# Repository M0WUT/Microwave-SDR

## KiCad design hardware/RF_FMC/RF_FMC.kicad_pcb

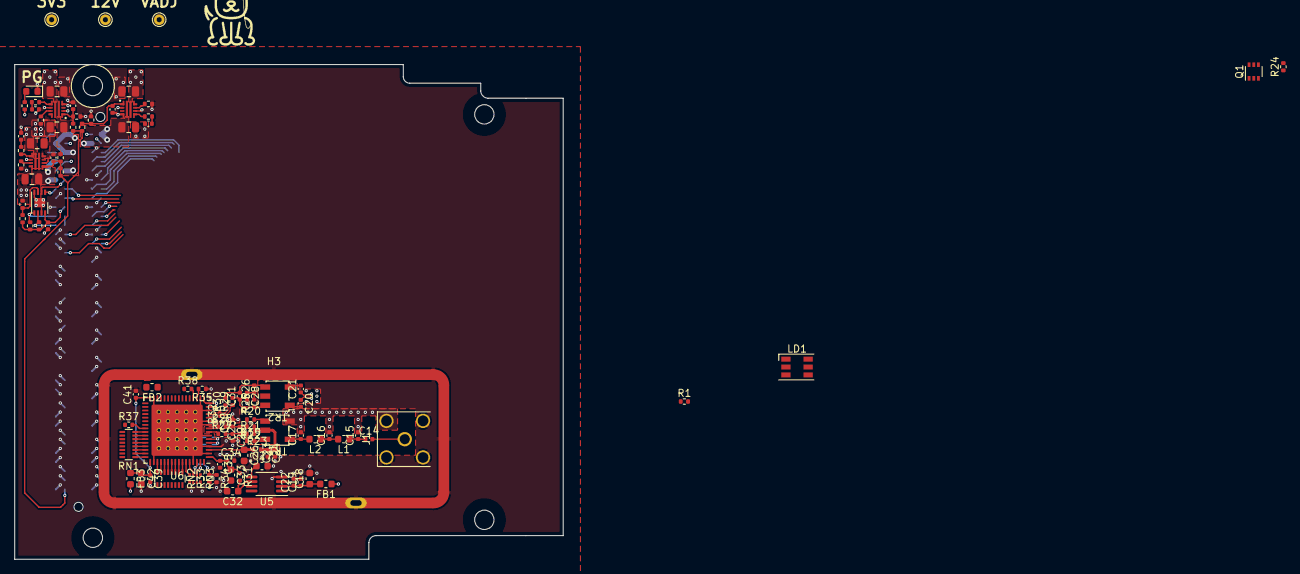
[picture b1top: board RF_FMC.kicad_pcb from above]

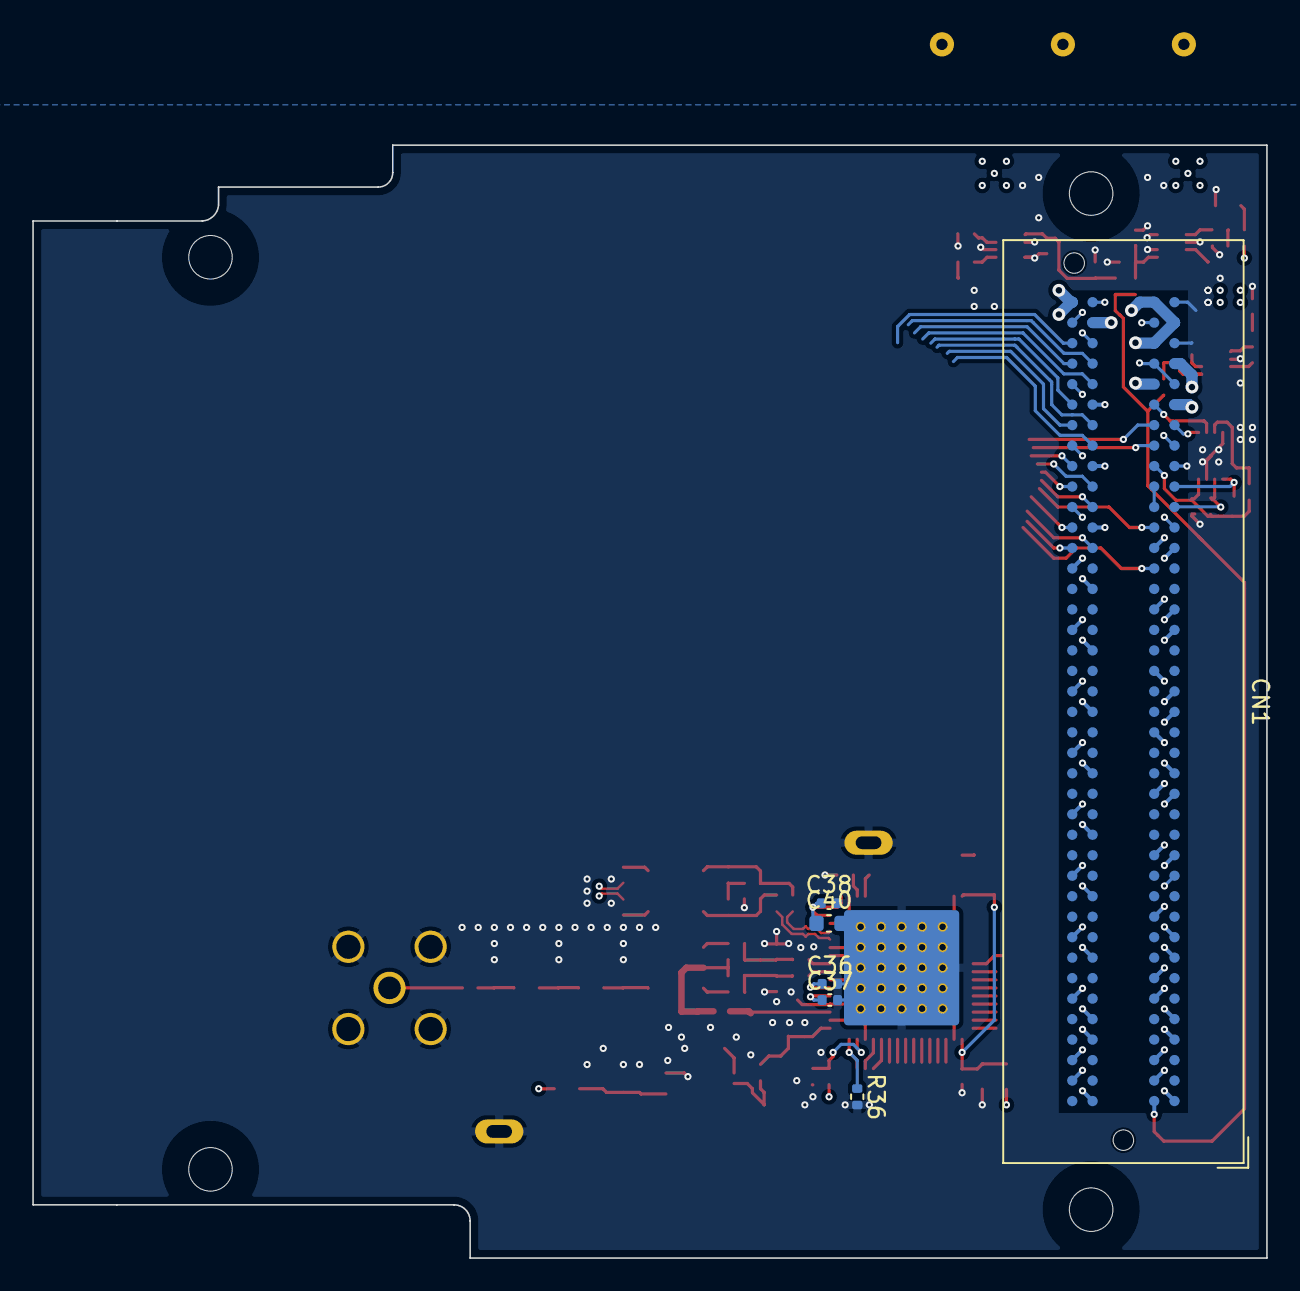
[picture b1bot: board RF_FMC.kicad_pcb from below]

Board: 4 copper layers, 76.5 x 69.0 mm, 108 parts (6 on the bottom side), 82 nets.

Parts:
C1, C14, C19, C20, C21, C24, C28, C34, C36, C37, C38, C39, C41: 100n; C_0402_1005Metric
C2, C3, C4, C11, C12, C13: 10u; C_0805_2012Metric
C5, C6, C7: DNF; C_0402_1005Metric
C8, C9, C10, C23: 10n; C_0402_1005Metric
C15, C17: 47p; C_0402_1005Metric
C16: 150p; C_0402_1005Metric
C18, C32, C33: 10u; C_0603_1608Metric
C22, C35: 1n; C_0402_1005Metric
C25, C29, C30, C31: 8p2; C_0402_1005Metric
C26: 2u2; C_0603_1608Metric
C27, C40, C42: 1u; C_0603_1608Metric
CN1: FMC_Mezzanine; Samtec_FMC_ASP-134604-01_4x40_Vertical
D1: LED; LED_0603_1608Metric
FB1, FB2, FB3: FerriteBead_Small; L_0603_1608Metric
H1, H2: MountingHole; MountingHole_2.7mm
H3: Shield; Shield_Masach_MS477-10_47.7x18.2x4mm_TH.step
J1: Conn_Coaxial; SMA_Linx_CONSMA002-L-G_Horizontal
L1, L2: 330n; L_0603_1608Metric
LD1: LED_Cree_CLX6E-FKC; LED_RGB_PLCC-6
M1: Logo_10mmx10mm
Q1: SI1539CDL-T1-GE3; SOT-363_SC-70-6
R1: R; R_0402_1005Metric
R2, R4, R5: DNF; R_0402_1005Metric
R3, R35: 0; R_0402_1005Metric
R6, R7, R8, R9: 1k; R_0402_1005Metric
R10, R11, R12: 100k; R_0402_1005Metric
R13, R14, R15: 100; R_0402_1005Metric
R16, R17, R18: 2k; R_0402_1005Metric
R19, R20: 10R; R_0402_1005Metric
R21, R22: 35R; R_0402_1005Metric
R23, R27, R28, R29, R30: 5R1; R_0402_1005Metric
R24: 22k; R_0402_1005Metric
R25, R26: 51R; R_0402_1005Metric
R31, R34, R36: 10k; R_0402_1005Metric
R32: 100R; R_0201_0603Metric
R33: 5k1; R_0402_1005Metric
R37, R38: 33; R_0402_1005Metric
RN1, RN2: 33; R_Array_Convex_8x0602
RN3: 33; R_Array_Convex_4x0402
TP1, TP2, TP3: TestPoint; TestPoint_THTPad_D1.5mm_Drill0.7mm
TR1, TR2: ETC1-1T-2TR; Macom_ETC-1xx
U1: 24LC02BT-I/MNY; DFN-8-1EP_3x2mm_P0.5mm_EP1.3x1.5mm
U2, U3, U4: LM73100RPWR; TI_LM73100_RPW
U5: REF5025IDGK; MSOP-8_3x3mm_P0.65mm
U6: LTC2216; QFN-64-1EP_9x9mm_P0.5mm_EP7.15x7.15mm

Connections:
3V3_AUX: C1.1, CN1.D32 (3P3VAUX), R2.1, R4.1, R5.1, U1.8 (VCC)
3V3_FMC: C3.1, CN1.C39 (3P3V), CN1.D36 (3P3V), CN1.D38 (3P3V), CN1.D40 (3P3V), U3.5 (IN)
12V_FMC: C2.1, CN1.C35 (12P0V), CN1.C37 (12P0V), U2.5 (IN)
+3.3VADC: FB1.1, FB2.2, LD1.4
+3V3: C12.1, R6.1, TP2.1, U3.6 (OUT)
+12V: C11.1, TP1.1, U2.6 (OUT)
/Direct Sampling ADC/ADC_Dither: R38.2, U6.20 (DITH)
/Direct Sampling ADC/ADC_N: C21.1, R1.2
/Direct Sampling ADC/ADC_P: C20.1, R1.1
/Direct Sampling ADC/ENC_N: R30.1, R32.2, U6.13 (ENC-)
/Direct Sampling ADC/ENC_P: R29.1, R32.1, U6.12 (ENC+)
/FMC Connector/FMC_SCL: CN1.C30 (SCL), R4.2, U1.6 (SCL)
/FMC Connector/FMC_SDA: CN1.C31 (SDA), R5.2, U1.5 (SDA)
/FMC Connector/GA0: CN1.C34 (GA0), U1.1 (A0)
/FMC Connector/GA1: CN1.D35 (GA1), U1.2 (A1)
/FMC Connector/PG_C2M: CN1.D1 (PG_C2M), R7.1, R8.1, R9.1
GND: C1.2, C2.2, C3.2, C4.2, C5.2, C6.2, C7.2, C8.2, C9.2, C10.2, C11.2, C12.2, C13.2, C15.2, C16.2, C17.2, C18.2, C19.2, C22.2, C23.1, C24.2, C26.2, C27.2, C28.2, C29.2, C30.2, C32.2, C33.2, C34.2, C35.2, C36.2, C37.2, C38.2, C39.2, C40.2, C41.2, C42.2, CN1.C1 (GND), CN1.C4 (GND), CN1.C5 (GND), CN1.C8 (GND), CN1.C9 (GND), CN1.C12 (GND), CN1.C13 (GND), CN1.C16 (GND), CN1.C17 (GND), CN1.C20 (GND), CN1.C21 (GND), CN1.C24 (GND), CN1.C25 (GND), CN1.C28 (GND), CN1.C29 (GND), CN1.C32 (GND), CN1.C33 (GND), CN1.C36 (GND), CN1.C38 (GND), CN1.C40 (GND), CN1.D2 (GND), CN1.D3 (GND), CN1.D6 (GND), CN1.D7 (GND), CN1.D10 (GND), CN1.D13 (GND), CN1.D16 (GND), CN1.D19 (GND), CN1.D22 (GND), CN1.D25 (GND), CN1.D28 (GND), CN1.D37 (GND), CN1.D39 (GND), CN1.G1 (GND), CN1.G4 (GND), CN1.G5 (GND), CN1.G8 (GND), CN1.G11 (GND), CN1.G14 (GND), CN1.G17 (GND), CN1.G20 (GND), CN1.G23 (GND), CN1.G26 (GND), CN1.G29 (GND), CN1.G32 (GND), CN1.G35 (GND), CN1.G38 (GND), CN1.G40 (GND), CN1.H2 (PRSNT_M2C_L), CN1.H3 (GND), CN1.H6 (GND), CN1.H9 (GND), CN1.H12 (GND), CN1.H15 (GND), CN1.H18 (GND), CN1.H21 (GND), CN1.H24 (GND), CN1.H27 (GND), CN1.H30 (GND), CN1.H33 (GND), CN1.H36 (GND), CN1.H39 (GND), D1.1 (K), H3.1, J1.2 (Ext), Q1.1, R3.2, R10.2, R11.2, R12.2, R16.2, R17.2, R18.2, R34.2, R35.1, R36.2, TR1.2, U1.4 (GND), U1.7 (WP), U1.9 (PAD), U2.2 (OVLO), U2.4 (PGTH), U2.8 (GND), U3.2 (OVLO), U3.4 (PGTH), U3.8 (GND), U4.2 (OVLO), U4.4 (PGTH), U4.8 (GND), U5.4 (GND), U6.2 (GND), U6.4 (GND), U6.7 (GND), U6.10 (GND), U6.11 (GND), U6.14 (GND), U6.18 (GND), U6.31 (OGND), U6.50 (OGND), U6.61 (LVDS), U6.65 (GND)
unnamed: C5.1, R7.2, R10.1, U2.1 (EN/UVLO)
unnamed: C6.1, R8.2, R11.1, U3.1 (EN/UVLO)
unnamed: C7.1, R9.2, R12.1, U4.1 (EN/UVLO)
unnamed: C8.1, R13.2
unnamed: C9.1, R14.2
unnamed: C10.1, R15.2
unnamed: C14.1, C15.1, L1.1
unnamed: C14.2, J1.1 (In)
unnamed: C16.1, L1.2, L2.1
unnamed: C17.1, L2.2, TR1.1
unnamed: C18.1, C19.1, C22.1, FB1.2, U5.2 (Vin)
unnamed: C20.2, TR2.1
unnamed: C21.2, TR2.2
unnamed: C23.2, C24.1, R21.2, R22.1, R23.2, TR1.4 (MP)
unnamed: C25.1, C29.1, R19.1, R21.1, R27.2
unnamed: C25.2, C30.1, R20.1, R22.2, R28.2
unnamed: C26.1, R23.1, U6.3 (VCM)
unnamed: C27.1, U5.5 (Trim/NR)
unnamed: C28.1, R25.2, R26.1
unnamed: C31.1, R25.1, R29.2, TR2.5
unnamed: C31.2, R26.2, R30.2, TR2.3
unnamed: C32.1, R31.2, U5.6 (Vout)
unnamed: C33.1, C34.1, C35.1, R31.1, U6.1 (Sense)
unnamed: CN1.D30 (TDI), CN1.D31 (TDO)
unnamed: D1.2 (A), R6.2
unnamed: LD1.3, R24.1
unnamed: Q1.6, R24.2
unnamed: R2.2, R3.1, U1.3 (A2)
unnamed: R13.1, U2.7 (DVDT)
unnamed: R14.1, U3.7 (DVDT)
unnamed: R15.1, U4.7 (DVDT)
unnamed: R16.1, U2.9 (IMON)
unnamed: R17.1, U3.9 (IMON)
unnamed: R18.1, U4.9 (IMON)
unnamed: R19.2, TR1.5
unnamed: R20.2, TR1.3
unnamed: R27.1, U6.8 (AIN+)
unnamed: R28.1, U6.9 (AIN-)
unnamed: R33.2, R34.1, U6.62 (Mode)
unnamed: R35.2, U6.19 (SHDN)
unnamed: R36.1, RN3.2 (R2.1), U6.63 (Rand)
unnamed: R37.2, U6.40 (ClkOutB)
unnamed: RN1.1 (R1.1), U6.48 (D6)
unnamed: RN1.2 (R2.1), U6.47 (D5)
unnamed: RN1.3 (R3.1), U6.46 (D4)
unnamed: RN1.4 (R4.1), U6.45 (D3)
unnamed: RN1.5 (R5.1), U6.44 (D2)
unnamed: RN1.6 (R6.1), U6.43 (D1)
unnamed: RN1.7 (R7.1), U6.42 (D0)
unnamed: RN1.8 (R8.1), U6.41 (ClkOutA)
unnamed: RN2.1 (R1.1), U6.58 (D14)
unnamed: RN2.2 (R2.1), U6.57 (D13)
unnamed: RN2.3 (R3.1), U6.56 (D12)
unnamed: RN2.4 (R4.1), U6.55 (D11)
unnamed: RN2.5 (R5.1), U6.54 (D10)
unnamed: RN2.6 (R6.1), U6.53 (D9)
unnamed: RN2.7 (R7.1), U6.52 (D8)
unnamed: RN2.8 (R8.1), U6.51 (D7)
unnamed: RN3.3 (R3.1), U6.60 (OF)
unnamed: RN3.4 (R4.1), U6.59 (D15)
OVDD: C39.1, C41.1, C42.1, FB3.1, U6.32 (OVDD), U6.49 (OVDD)
RF_ADC_Overflow: Q1.2, RN3.6 (R3.2)
VADJ: C13.1, FB3.2, TP3.1, U4.6 (OUT)
VADJ_FMC: C4.1, CN1.G39 (VADJ), CN1.H40 (VADJ), U4.5 (IN)
VDD: C36.1, C37.1, C38.1, C40.1, FB2.1, R33.1, U6.5 (VDD), U6.6 (VDD), U6.15 (VDD), U6.16 (VDD), U6.17 (VDD)

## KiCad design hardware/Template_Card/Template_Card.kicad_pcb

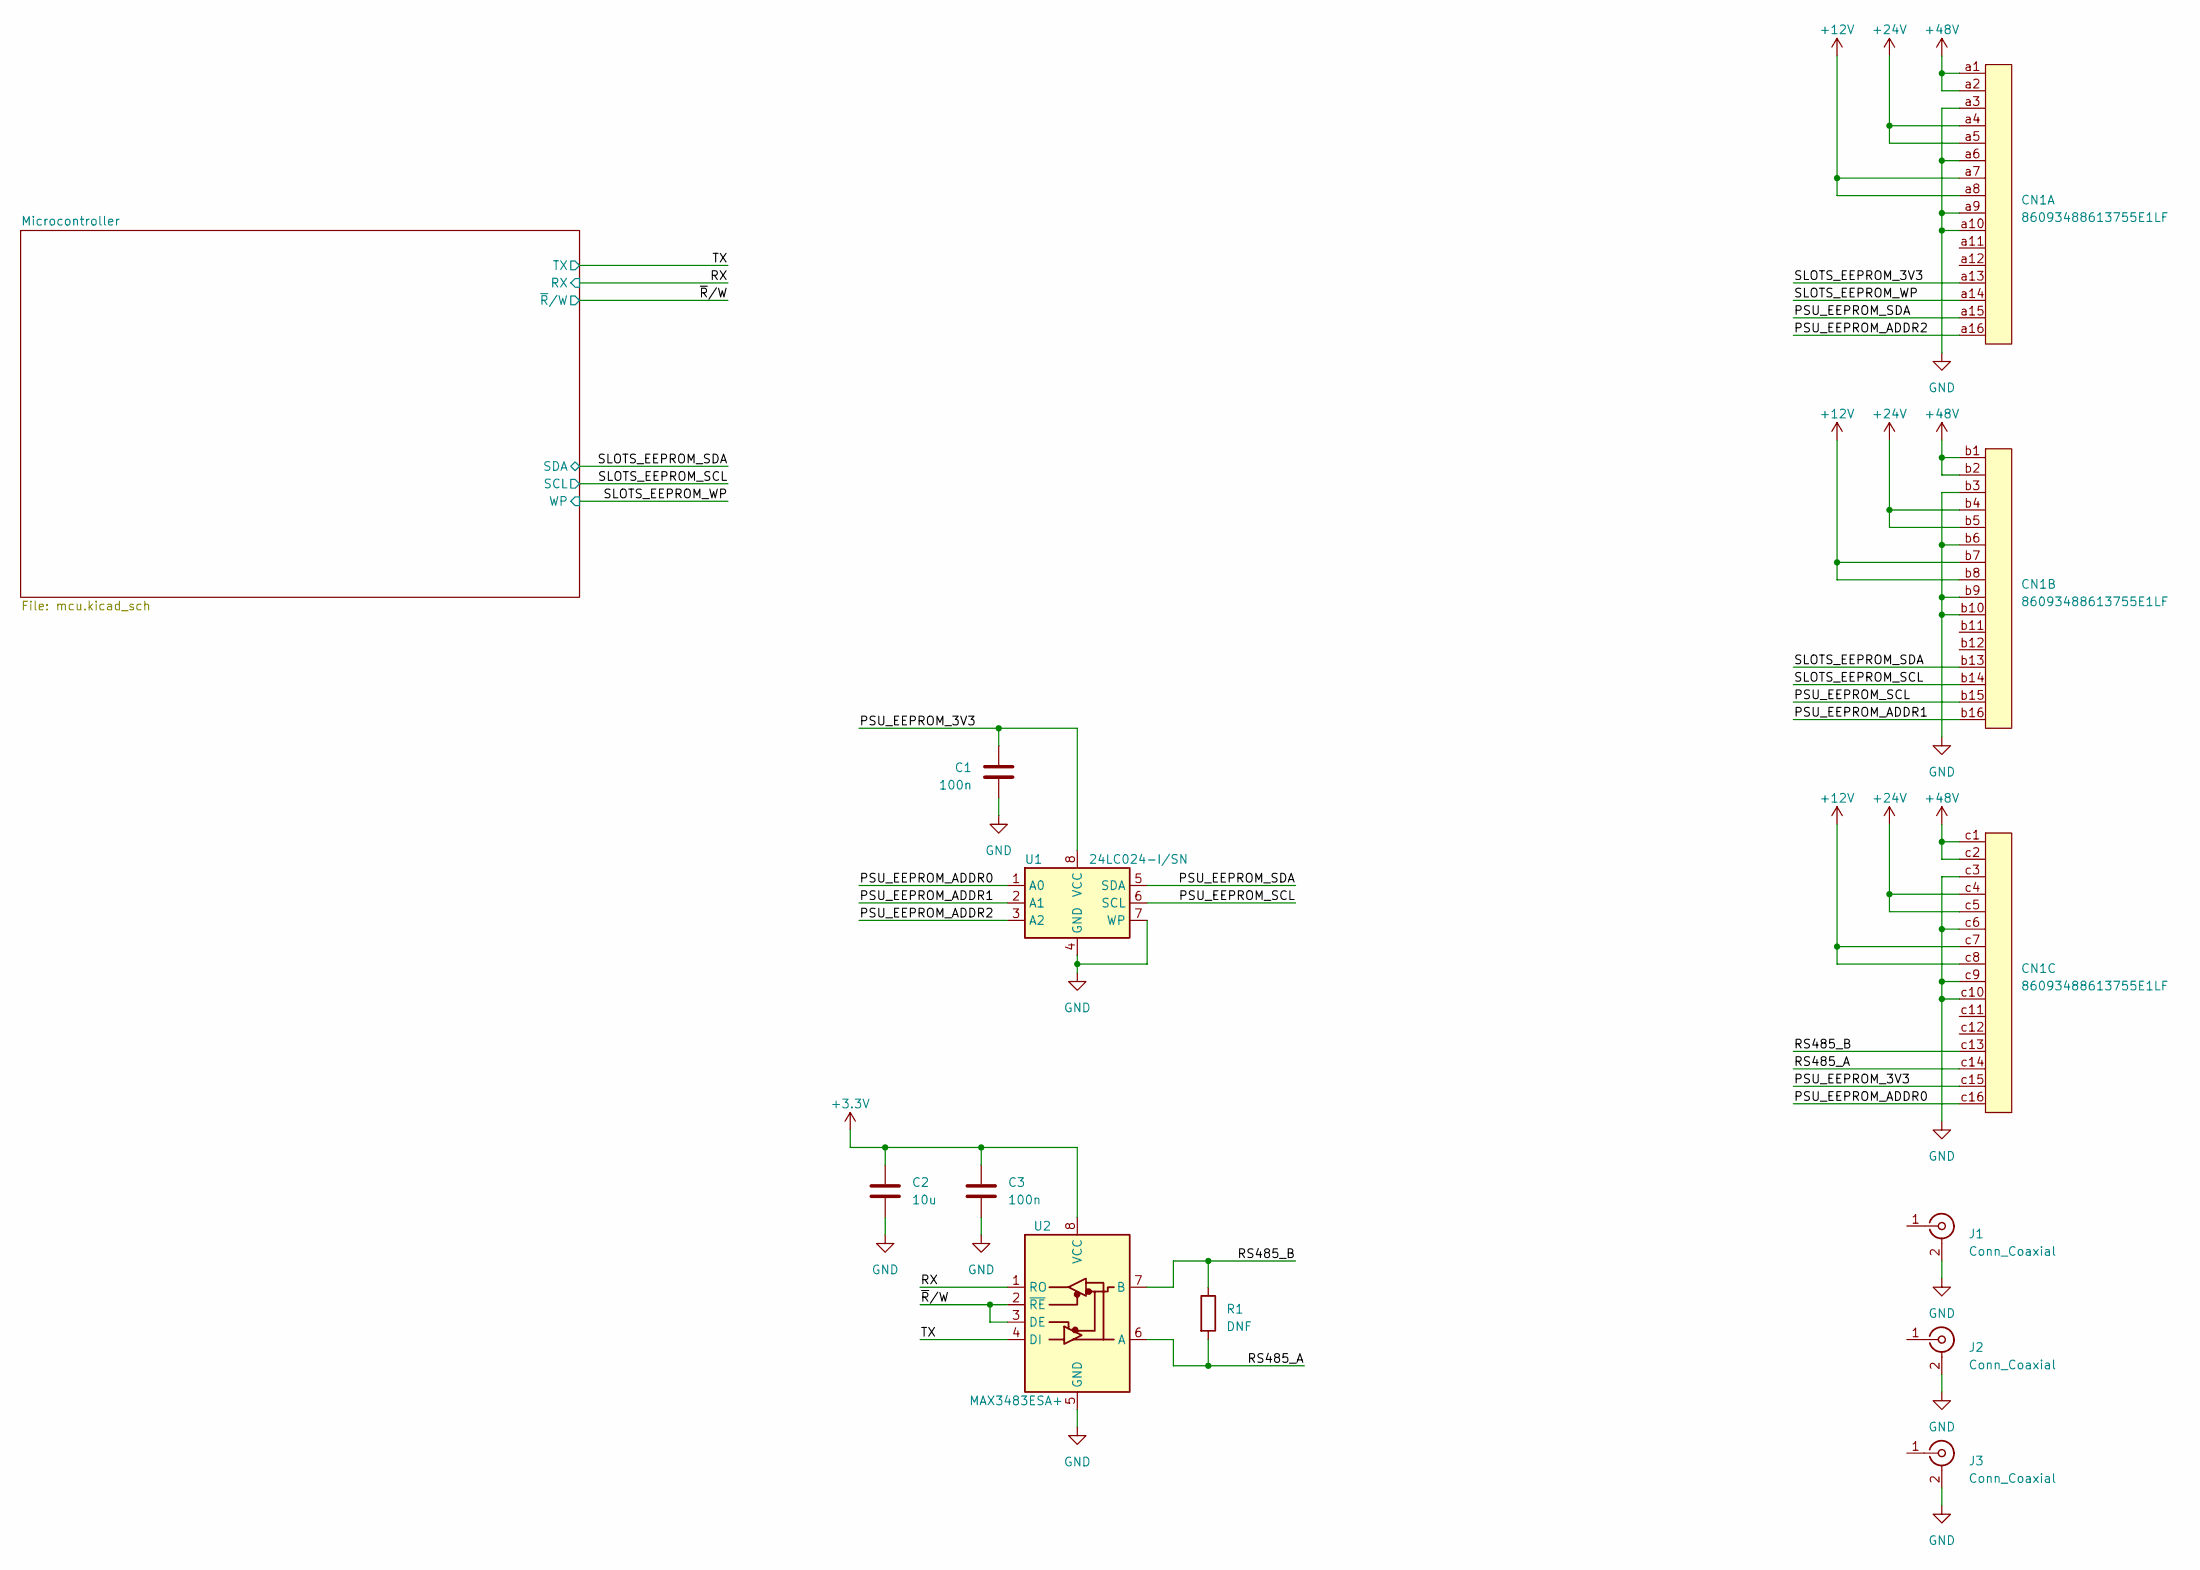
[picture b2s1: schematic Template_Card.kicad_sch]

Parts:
C1, C3: 100n; C_0402_1005Metric
C2: 10u; C_0603_1608Metric
CN1: 86093488613755E1LF; DIN41612_R_03x16_Receptacle_RA_Amphenol_86093488613755E1LF
J1, J2, J3: Conn_Coaxial; SMA_Linx_CONSMA002-L-G_Horizontal
R1: DNF; R_0603_1608Metric
U1: 24LC024-I/SN; SOIC-8_3.9x4.9mm_P1.27mm
U2: MAX3483ESA+; SOIC-8_3.9x4.9mm_P1.27mm

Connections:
+12V: CN1.a7, CN1.a8, CN1.b7, CN1.b8, CN1.c7, CN1.c8
+24V: CN1.a4, CN1.a5, CN1.b4, CN1.b5, CN1.c4, CN1.c5
+48V: CN1.a1, CN1.a2, CN1.b1, CN1.b2, CN1.c1, CN1.c2
/PSU_EEPROM_3V3: C1.1, CN1.c15, U1.8 (VCC)
/PSU_EEPROM_ADDR0: CN1.c16, U1.1 (A0)
/PSU_EEPROM_ADDR1: CN1.b16, U1.2 (A1)
/PSU_EEPROM_ADDR2: CN1.a16, U1.3 (A2)
/PSU_EEPROM_SCL: CN1.b15, U1.6 (SCL)
/PSU_EEPROM_SDA: CN1.a15, U1.5 (SDA)
/RS485_A: CN1.c14, R1.2, U2.6 (A)
/RS485_B: CN1.c13, R1.1, U2.7 (B)
/RX: U2.1 (RO); also elsewhere on the board
/SLOTS_EEPROM_3V3: CN1.a13
/SLOTS_EEPROM_SCL: CN1.b14; also elsewhere on the board
/SLOTS_EEPROM_SDA: CN1.b13; also elsewhere on the board
/SLOTS_EEPROM_WP: CN1.a14; also elsewhere on the board
/TX: U2.4 (DI); also elsewhere on the board
/~R/W: U2.2 (~RE), U2.3 (DE); also elsewhere on the board
GND: C1.2, C2.2, C3.2, CN1.a3, CN1.a6, CN1.a9, CN1.a10, CN1.b3, CN1.b6, CN1.b9, CN1.b10, CN1.c3, CN1.c6, CN1.c9, CN1.c10, J1.2 (Ext), J2.2 (Ext), J3.2 (Ext), U1.4 (GND), U1.7 (WP), U2.5 (GND); also elsewhere on the board

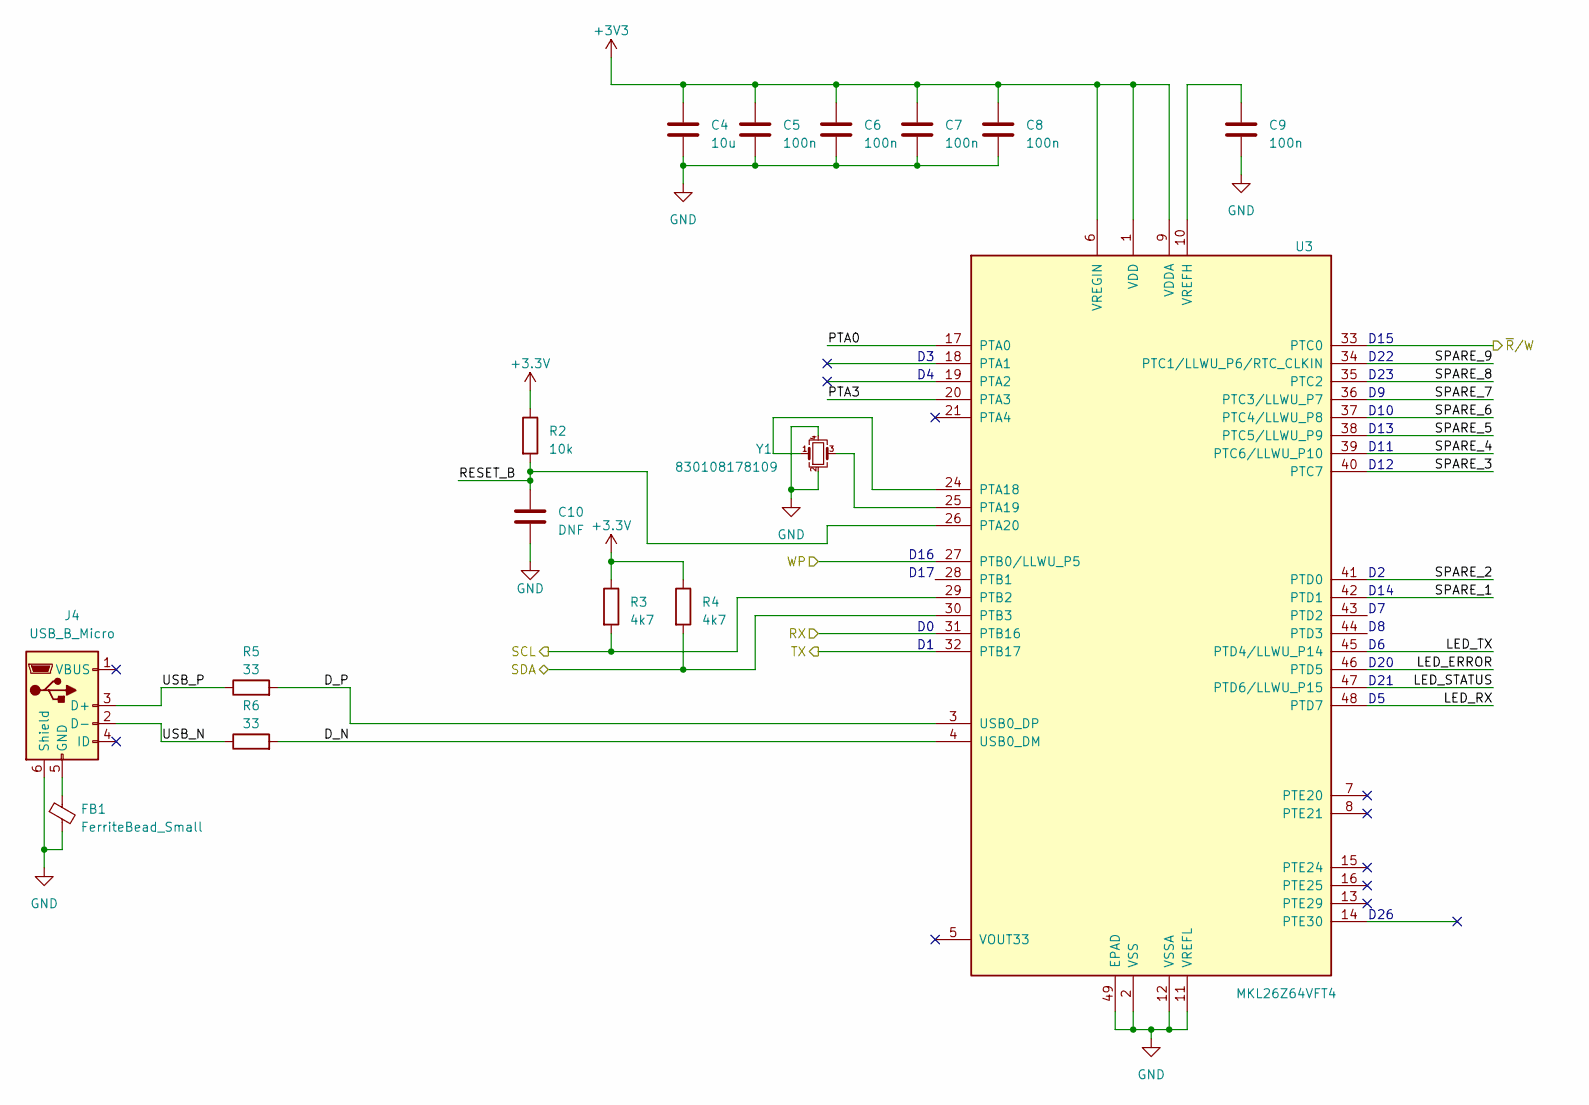
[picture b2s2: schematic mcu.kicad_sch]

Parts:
C4: 10u; C_0603_1608Metric
C5, C6, C7, C8, C9: 100n; C_0402_1005Metric
C10: DNF; C_0402_1005Metric
FB1: FerriteBead_Small; L_0603_1608Metric
J4: USB_B_Micro; USB_MicroB_Molex_105133-001_Vertical
R2: 10k; R_0402_1005Metric
R3, R4: 4k7; R_0402_1005Metric
R5, R6: 33; R_0402_1005Metric
U3: MKL26Z64VFT4; QFN-48-1EP_7x7mm_P0.5mm_EP5.15x5.15mm
Y1: 830108178109; Crystal_SMD_2016-4Pin_2.0x1.6mm

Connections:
/Microcontroller/D_N: R6.2, U3.4 (USB0_DM)
/Microcontroller/D_P: R5.2, U3.3 (USB0_DP)
/Microcontroller/LED_ERROR: U3.46 (PTD5)
/Microcontroller/LED_RX: U3.48 (PTD7)
/Microcontroller/LED_STATUS: U3.47 (PTD6/LLWU_P15)
/Microcontroller/LED_TX: U3.45 (PTD4/LLWU_P14)
/Microcontroller/PTA0: U3.17 (PTA0)
/Microcontroller/PTA3: U3.20 (PTA3)
/Microcontroller/RESET_B: C10.1, R2.2, U3.26 (PTA20)
/Microcontroller/SPARE_1: U3.42 (PTD1)
/Microcontroller/SPARE_2: U3.41 (PTD0)
/Microcontroller/SPARE_3: U3.40 (PTC7)
/Microcontroller/SPARE_4: U3.39 (PTC6/LLWU_P10)
/Microcontroller/SPARE_5: U3.38 (PTC5/LLWU_P9)
/Microcontroller/SPARE_6: U3.37 (PTC4/LLWU_P8)
/Microcontroller/SPARE_7: U3.36 (PTC3/LLWU_P7)
/Microcontroller/SPARE_8: U3.35 (PTC2)
/Microcontroller/SPARE_9: U3.34 (PTC1/LLWU_P6/RTC_CLKIN)
/Microcontroller/USB_N: J4.2 (D-), R6.1
/Microcontroller/USB_P: J4.3 (D+), R5.1
/RX: U3.31 (PTB16); also elsewhere on the board
/SLOTS_EEPROM_SCL: R3.2, U3.29 (PTB2); also elsewhere on the board
/SLOTS_EEPROM_SDA: R4.2, U3.30 (PTB3); also elsewhere on the board
/SLOTS_EEPROM_WP: U3.27 (PTB0/LLWU_P5); also elsewhere on the board
/TX: U3.32 (PTB17); also elsewhere on the board
/~R/W: U3.33 (PTC0); also elsewhere on the board
GND: C4.2, C5.2, C6.2, C7.2, C8.2, C9.2, C10.2, FB1.2, J4.6 (Shield), U3.2 (VSS), U3.11 (VREFL), U3.12 (VSSA), U3.23 (VSS), U3.49 (EPAD), Y1.2, Y1.4; also elsewhere on the board
unnamed: C9.1, U3.10 (VREFH)
unnamed: FB1.1, J4.5 (GND)
unnamed: U3.24 (PTA18), Y1.1
unnamed: U3.25 (PTA19), Y1.3

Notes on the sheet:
D16
D17
D15
D22
D23
D10
D13
D11
D12
D14
D20
D21
D26

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
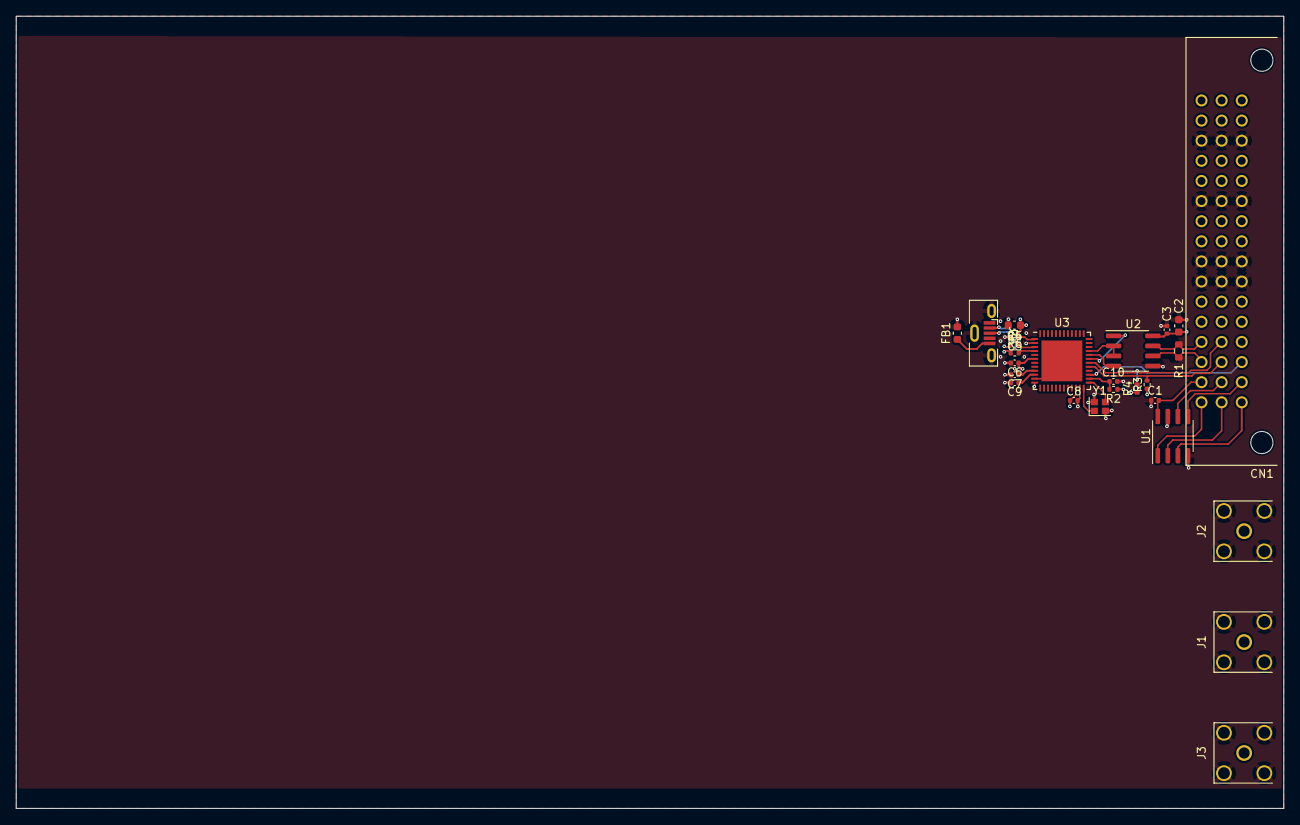
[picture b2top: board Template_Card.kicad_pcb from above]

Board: 4 copper layers, 160.0 x 100.0 mm, 26 parts (0 on the bottom side), 28 nets.

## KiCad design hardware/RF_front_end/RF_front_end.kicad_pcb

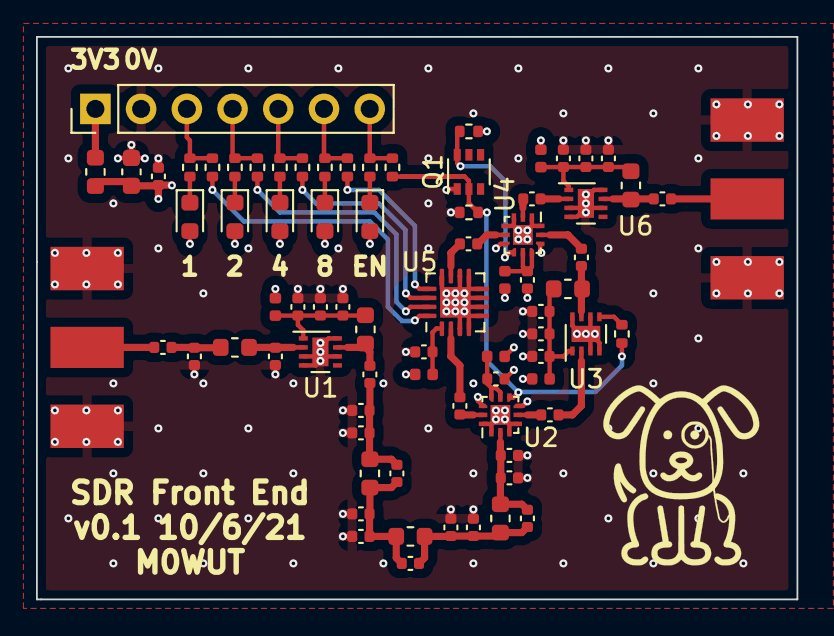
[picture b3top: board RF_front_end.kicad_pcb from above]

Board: 4 copper layers, 42.2 x 31.2 mm, 78 parts (0 on the bottom side), 46 nets.

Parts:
C1, C2, C4, C25, C26, C27, C28, C29, C30, C31, C32, C33, C34, C35: C; C_0402_1005Metric
C3: 10u; C_0603_1608Metric
C5: 1u; C_0402_1005Metric
C6, C7, C8, C9, C11, C12, C13, C14, C16, C17, C18, C19, C20, C21, C23, C24: 100n; C_0402_1005Metric
C10, C15, C22: 10u; C_0402_1005Metric
D1, D2, D3, D4, D5: LED; LED_0603_1608Metric
FB1: FerriteBead_Small; L_0603_1608Metric
FB2, FB3, FB4, FB5, FB6, FB7: FerriteBead_Small; L_0402_1005Metric
J1, J3: Conn_Coaxial; SMA_Molex_73251-1150_EdgeMount_Horizontal
J2: Conn_01x07_Male; PinHeader_1x07_P2.54mm_Vertical
L1, L5, L6, L7: L; L_0603_1608Metric
L2, L3, L4: 0603LS-392X_R_; L_0603_1608Metric
M1: Logo_10mmx10mm
Q1: SI1539CDL-T1-GE3; SOT-363_SC-70-6
R1, R2, R3, R4, R5: 1k; R_0402_1005Metric
R6, R7, R8, R9, R10: 100; R_0402_1005Metric
R11: 0; R_0402_1005Metric
R12, R13: 10k; R_0402_1005Metric
U1, U3, U6: TRF37D73; WSON-8-1EP_2x2mm_P0.5mm_EP0.9x1.6mm
U2, U4: F2972NEGK; Renesas_QFN-12-1EP_2x2mm_P0.5mm_EP1.1x1.1mm
U5: RFSA3413; QFN-16-1EP_3x3mm_P0.5mm_EP1.7x1.7mm

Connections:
+3V3: C3.1, C5.1, D1.2 (A), D2.2 (A), D3.2 (A), D4.2 (A), D5.2 (A), FB1.2, FB2.1, FB3.1, FB4.1, FB5.1, FB6.1, FB7.1, R13.1
/20dB Gain Block1/PWRDN: R11.2, U3.5 (PWDN)
/20dB Gain Block1/RFIN: C6.2, U3.2 (RFIN)
/20dB Gain Block1/RFOUT: C17.2, U4.11 (RF2)
/20dB Gain Block2/RFIN: C8.2, U6.2 (RFIN)
/20dB Gain Block2/RFOUT: C24.2, J3.1 (In)
/20dB Gain Block/RFIN: C4.1, L1.2, U1.2 (RFIN)
/20dB Gain Block/RFOUT: C12.2, C25.1, C26.1, C27.1, L5.1
/ATT0: R6.2, U5.16 (C1)
/ATT1: R9.2, U5.15 (C2)
/ATT2: R7.2, U5.14 (C4)
/ATT3: R10.2, U5.13 (C8)
/ATT_EN: Q1.2, R8.2, R11.1, R12.1, U2.7 (VCTL)
/Adjustable Attenuator/RFIN: C7.2, U5.2 (RFIN)
/Adjustable Attenuator/RFOUT: C20.2, U4.5 (RF1)
/Generic Filter/RFOUT: C33.2, C34.1, C35.1, L7.2, U2.2 (RFC)
/RF Switch1/RFC: C8.1, U4.2 (RFC)
/RF Switch1/VCTL: Q1.6, R13.2, U4.7 (VCTL)
/RF Switch/RF1: C6.1, U2.5 (RF1)
/RF Switch/RF2: C7.1, U2.11 (RF2)
GND: C2.2, C3.2, C4.2, C5.2, C9.2, C10.2, C11.2, C13.2, C14.2, C15.2, C16.2, C18.2, C19.2, C21.2, C22.2, C23.2, C25.2, C26.2, C28.2, C29.2, C31.2, C32.2, C34.2, C35.2, J1.2 (Ext), J2.2, J3.2 (Ext), Q1.1, R12.2, U1.3 (NC), U1.4 (NC), U1.6 (NC), U1.8 (NC), U1.9 (PAD), U2.1 (GND), U2.3 (GND), U2.4 (GND), U2.6 (GND), U2.10 (GND), U2.12 (GND), U2.13 (PAD), U3.3 (NC), U3.4 (NC), U3.6 (NC), U3.8 (NC), U3.9 (PAD), U4.1 (GND), U4.3 (GND), U4.4 (GND), U4.6 (GND), U4.10 (GND), U4.12 (GND), U4.13 (PAD), U5.3 (NC), U5.4 (NC), U5.5 (NC), U5.6 (NC), U5.7 (NC), U5.8 (NC), U5.9 (NC), U5.10 (NC), U5.12 (NC), U5.17 (PAD), U6.3 (NC), U6.4 (NC), U6.6 (NC), U6.8 (NC), U6.9 (PAD)
unnamed: C1.1, J1.1 (In)
unnamed: C1.2, C2.1, L1.1
unnamed: C9.1, C10.1, C11.1, FB2.2, L2.1, U1.1 (VCC)
unnamed: C12.1, L2.2, U1.7 (RFOUT)
unnamed: C13.1, FB3.2, U2.8 (EN), U2.9 (VCC)
unnamed: C14.1, C15.1, C16.1, FB4.2, L3.1, U3.1 (VCC)
unnamed: C17.1, L3.2, U3.7 (RFOUT)
unnamed: C18.1, FB5.2, U4.8 (EN), U4.9 (VCC)
unnamed: C19.1, FB6.2, U5.1 (VDD)
unnamed: C20.1, U5.11 (RFOUT)
unnamed: C21.1, C22.1, C23.1, FB7.2, L4.1, U6.1 (VCC)
unnamed: C24.1, L4.2, U6.7 (RFOUT)
unnamed: C27.2, C28.1, C29.1, C30.1, L5.2, L6.1
unnamed: C30.2, C31.1, C32.1, C33.1, L6.2, L7.1
unnamed: D1.1 (K), R1.1
unnamed: D2.1 (K), R2.1
unnamed: D3.1 (K), R3.1
unnamed: D4.1 (K), R4.1
unnamed: D5.1 (K), R5.1
unnamed: FB1.1, J2.1
unnamed: J2.3, R1.2, R6.1
unnamed: J2.4, R2.2, R9.1
unnamed: J2.5, R3.2, R7.1
unnamed: J2.6, R4.2, R10.1
unnamed: J2.7, R5.2, R8.1

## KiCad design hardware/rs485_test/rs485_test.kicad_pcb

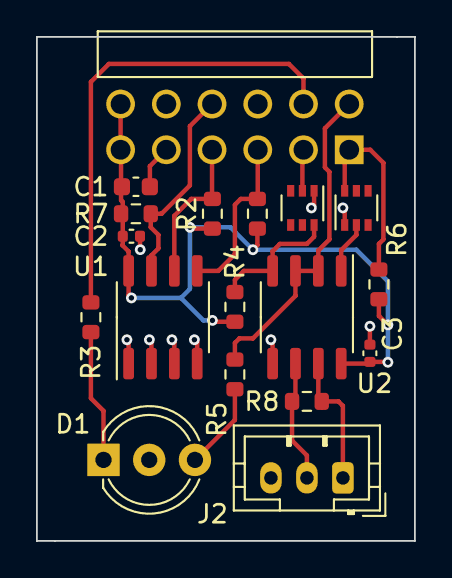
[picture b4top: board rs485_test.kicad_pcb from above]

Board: 2 copper layers, 21.0 x 28.0 mm, 18 parts (0 on the bottom side), 15 nets.

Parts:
C1: 10u; C_0603_1608Metric
C2, C3: 100n; C_0402_1005Metric
D1: LED_Dual_AKA; LED_D5.0mm-3
J1: Connector_PMOD_2x6_Peripheral; PMOD_Wurth_61301221021_Horizontal
J2: Conn_01x03_Male; JST_PH_B3B-PH-K_1x03_P2.00mm_Vertical
Q1, Q2: SI1539CDL-T1-GE3; SOT-363_SC-70-6
R1, R2: 4k7; R_0603_1608Metric
R3, R5, R6: R; R_0603_1608Metric
R4: 10k; R_0603_1608Metric
R7: 1k; R_0603_1608Metric
R8: 120; R_0603_1608Metric
U1: 24LC024-I/SN; SO-8_3.9x4.9mm_P1.27mm
U2: MAX3483ESA+; SO-8_3.9x4.9mm_P1.27mm

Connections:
+3V3: C1.1, C2.1, C3.1, J1.6 (+3V3), J1.12 (+3V3), R1.1, R2.1, R4.1, R6.1, R7.1, U1.8 (VCC), U2.8 (VCC)
/SCL: J1.4, R2.2, U1.6 (SCL)
/SDA: J1.3, R1.2, U1.5 (SDA)
/~WP: J1.10, R7.2, U1.7 (WP)
GND: C1.2, C2.2, C3.2, D1.2 (K), J1.5 (GND), J1.11 (GND), J2.3, Q1.1, Q2.1, U1.1 (A0), U1.2 (A1), U1.3 (A2), U1.4 (GND), U2.5 (GND)
unnamed: D1.1 (A1), R3.2
unnamed: D1.3 (A2), R5.2
unnamed: J1.1, Q2.6, R6.2
unnamed: J1.2, Q1.2
unnamed: J1.7, R5.1, U2.2 (~RE), U2.3 (DE)
unnamed: J1.8, R3.1
unnamed: J2.1, R8.1, U2.7 (B)
unnamed: J2.2, R8.2, U2.6 (A)
unnamed: Q1.6, R4.2, U2.4 (DI)
unnamed: Q2.2, U2.1 (RO)

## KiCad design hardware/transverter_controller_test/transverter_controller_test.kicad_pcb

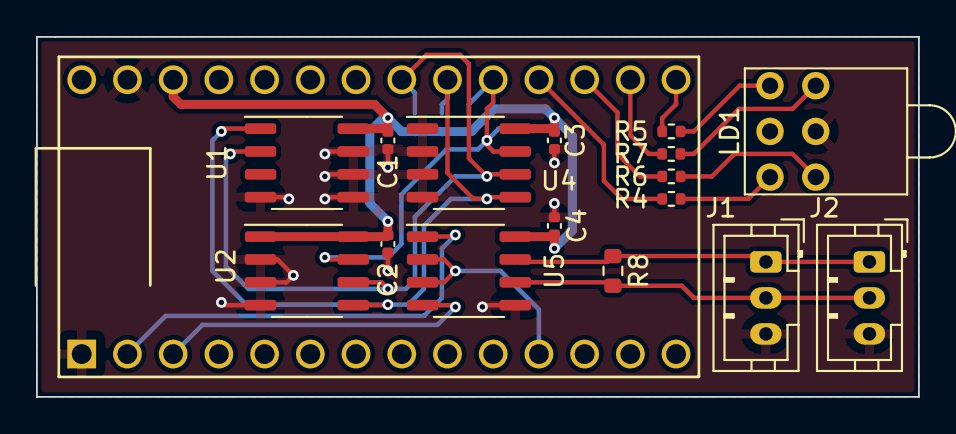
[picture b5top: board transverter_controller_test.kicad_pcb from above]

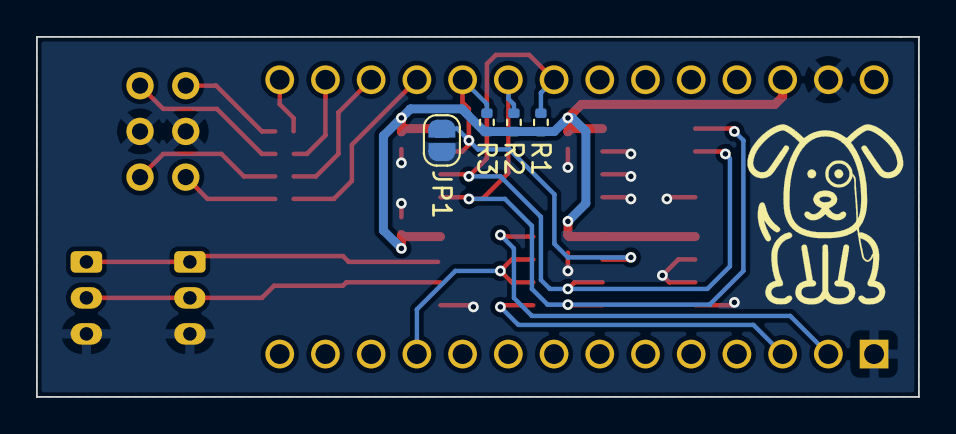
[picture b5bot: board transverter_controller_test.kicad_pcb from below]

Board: 2 copper layers, 49.0 x 20.0 mm, 22 parts (5 on the bottom side), 18 nets.

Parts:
C1, C2, C3, C4: 100n; C_0402_1005Metric
J1, J2: Conn_01x03_Male; JST_PH_B3B-PH-K_1x03_P2.00mm_Vertical
JP1: SolderJumper_2_Open; SolderJumper-2_P1.3mm_Open_RoundedPad1.0x1.5mm
LD1: Kingbright_WP130WCP_2EGW
M1: Logo_10mmx10mm
R1, R2: 4k7; R_0402_1005Metric
R3, R4, R5, R6, R7: 1k; R_0402_1005Metric
R8: DNF; R_0603_1608Metric
U1: PCT2075D; SO-8_3.9x4.9mm_P1.27mm
U2, U4: 24LC024-I/SN; SO-8_3.9x4.9mm_P1.27mm
U3: Teensy-LC; Teensy_LC
U5: MAX3483ESA+; SO-8_3.9x4.9mm_P1.27mm

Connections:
+3V3: C1.1, C2.1, C3.1, C4.1, R1.1, R2.1, R3.1, U1.8 (VCC), U2.1 (A0), U2.8 (VCC), U3.31 (3.3V), U4.8 (VCC), U5.8 (VCC)
/LED_ERROR: R6.1, U3.22 (15_A1_Touch)
/LED_RX: R5.1, U3.20 (13_LED_SCK0)
/LED_STATUS: R7.1, U3.21 (14_A0_SCK0)
/LED_TX: R4.1, U3.23 (16_A2_SCL0_PWM_Touch)
/RX: U3.2 (0_RX1_MOSI1_Touch), U5.1 (RO)
/SCL: R1.2, U1.2 (SCL), U2.6 (SCL), U3.26 (19_A5_SCL0_Touch), U4.6 (SCL)
/SDA: R2.2, U1.1 (SDA), U2.5 (SDA), U3.25 (18_A4_SDA0_Touch), U4.5 (SDA)
/TX: U3.3 (1_TX1_MISO1_Touch), U5.4 (DI)
/WP: JP1.1 (A), R3.2, U2.7 (WP), U3.24 (17_A3_SDA0_PWM_Touch), U4.7 (WP)
/~R~/W: U3.11 (9_RX2_PWM), U5.2 (~RE), U5.3 (DE)
GND: C1.2, C2.2, C3.2, C4.2, J1.3, J2.3, JP1.2 (B), LD1.2, LD1.5, U1.4 (GND), U1.5 (A2), U1.6 (A1), U1.7 (A0), U2.2 (A1), U2.3 (A2), U2.4 (GND), U3.1 (GND), U3.32 (GND), U4.1 (A0), U4.2 (A1), U4.3 (A2), U4.4 (GND), U5.5 (GND)
unnamed: J1.1, J2.1, R8.1, U5.7 (B)
unnamed: J1.2, J2.2, R8.2, U5.6 (A)
unnamed: LD1.1, R4.2
unnamed: LD1.3, R5.2
unnamed: LD1.4, R6.2
unnamed: LD1.6, R7.2

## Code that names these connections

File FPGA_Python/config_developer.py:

from gpio import AxiGpio, GPIO

LED_ERROR = AxiGpio(1, GPIO.OUTPUT)
LED_STATUS = AxiGpio(3, GPIO.OUTPUT)
PIN_RS485_TX = AxiGpio(2, GPIO.OUTPUT)
LED_RX = AxiGpio(4, GPIO.OUTPUT)
LED_TX = AxiGpio(0, GPIO.OUTPUT)
PIN_WP = AxiGpio(5, GPIO.INPUT)

SLOTS_I2C_FILE = "/dev/i2c-0"
SLOTS_EEPROM_ADDRESS = 0x50

STATUS_REGISTERS_FILE = "/dev/statusregs"

TRANSVERTER_RS485_UART = "/dev/ttyPS1"

MQTT_API_VERSION = "0.0.1w"

NUM_CHANNELS = 1

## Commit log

2021-05-04 Unified commit with tcl script
2021-05-04 added constraints files
2021-05-04 Added testbench waveform as apparently it's super important
2021-05-04 Trying adding more of the Vivado project
2021-05-04 Attempting to replace TCL and just backup project
2021-05-05 Started thinking about transverter controller
2021-05-06 Basic transverter discovery working
2021-05-07 Improved Teensy handling of discovery packets
2021-05-08 v1 transverter interface complete
2021-05-09 Started work on RS485 board
2021-05-09 updated kicad gitignore
2021-05-10 Added RS485 driver and AXI GPIO for read/write
2021-05-11 RS485 now tranmitting from FPGA and received by transverters
2021-05-12 Now loading RS485 address from EEPROM
2021-05-13 added FPGA board
2021-05-13 Fixed submodule linking
2021-05-13 Tidied some Arduino code into classes
2021-05-14 Bidirectional RS485 now working
2021-05-14 Moved to Platform IO based structure for transverter code
2021-05-15 SSB RX working in isolation!
2021-06-02 Added RS485 test board
2021-06-06 More work on IF stage
2021-06-08 More work on front end
2021-06-10 Finished front end
2021-06-16 Massive shuffle of Transverter code to be Arduino compatible
2021-06-17 Got temperature sensor working
2021-06-18 Faffed with moving more stuff into config files. Now locks up when reading temperature
2021-06-20 Now supports multiple temperature sensors
2021-06-20 Address EEPROM initialisation now behaving
2021-06-20 stuff
2021-06-21 RS485 working properly now
2021-06-22 Completed discovery message
2021-06-25 Started adding I2C EEPROM
2021-06-26 I2C Device now working
2021-06-26 Transverter detection now being reported to Pi
2021-06-28 Started documentation in Word, created template card
2021-07-01 More work on template card
2021-07-05 More work on spec
2021-07-07 added RX support to transverter info
2021-07-07 Updated transverter discovery / status
2021-07-09 Network discovery of SDR cards now supported
2021-07-10 Basic status messaging now working
2021-07-11 Now getting and displaying status info from transverters
2021-07-13 Nicely refreshing transverters and updating status colours
2021-07-13 Moved card labels to buttons to allow card detailed info to be shown
2021-07-13 Removed some unecessary inheritance added during debug
2021-07-14 Now force NTP sync before starting program
2021-07-15 Fixed stylesheet import to happen before making custom fonts
2021-07-25 Added frequency entry via keypad
2021-08-08 Finished discovery section of documentation
2021-08-13 Updated to match Documentation
2021-08-13 Added requirement for cards to report their address back to the discovery commands
2021-08-19 Started to add transverter selection
2021-08-20 Removed a lot of unecessary code from FPGA Python
2021-08-21 Progress on transverter control requests
2021-08-21 In a broken state but barebones of requests are now working
2021-08-22 Transverter request now working properly
2021-08-22 Transverter release now working
2021-09-20 Started on soldering test board
2021-09-22 Started on FMC card template
2021-09-23 Redid FMC template to parts I can actually buy!
2021-09-24 Now working on FMC card from template
2021-09-26 Started on ADC layout
2021-10-03 Now with SSB RX
2021-10-23 backup before attempting silly things
2021-10-23 Fixed issue with ADC input not latching data
2022-11-23 Pc upgrade
